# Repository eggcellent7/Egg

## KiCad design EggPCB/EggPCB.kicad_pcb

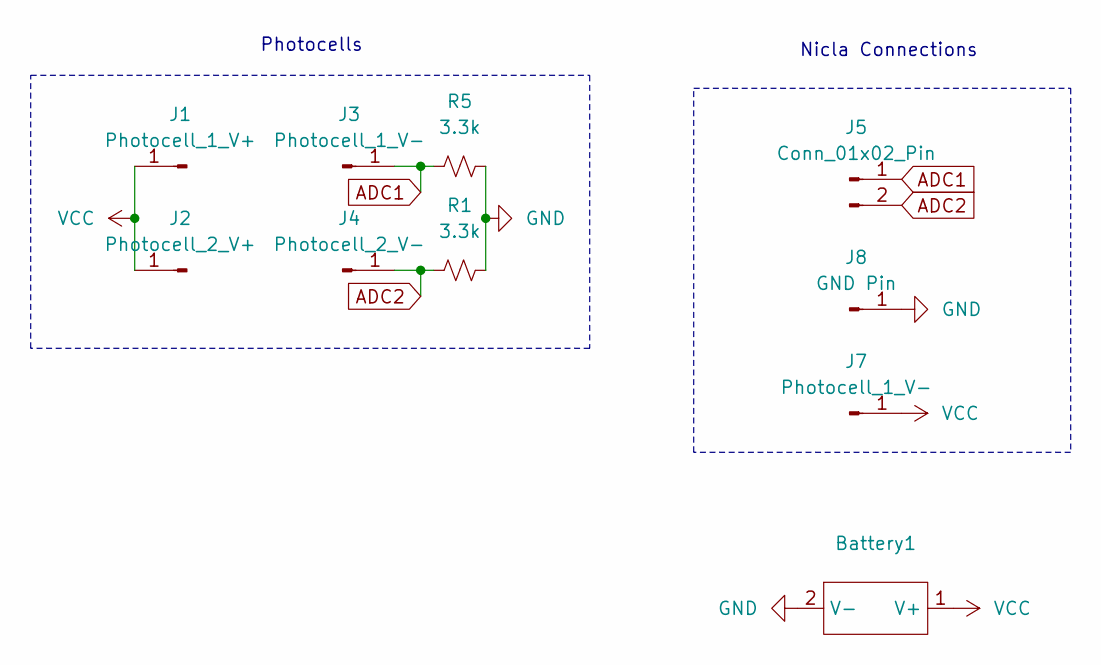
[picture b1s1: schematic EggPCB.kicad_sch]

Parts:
Battery1: CoinCellBat
J1: Photocell_1_V+; PinHeader_1x01_P2.54mm_Vertical
J2: Photocell_2_V+; PinHeader_1x01_P2.54mm_Vertical
J3, J7: Photocell_1_V-; PinHeader_1x01_P2.54mm_Vertical
J4: Photocell_2_V-; PinHeader_1x01_P2.54mm_Vertical
J5: Conn_01x02_Pin; PinHeader_1x02_P2.54mm_Vertical
J8: GND Pin; PinHeader_1x01_P2.54mm_Vertical
R1, R5: 3.3k; R_Axial_DIN0207_L6.3mm_D2.5mm_P7.62mm_Horizontal

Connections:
ADC1: J3.1, J5.1, R5.1
ADC2: J4.1, J5.2, R1.1
GND: Battery1.2 (V-), J8.1, R1.2, R5.2
VCC: Battery1.1 (V+), J1.1, J2.1, J7.1

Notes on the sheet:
Photocells
Nicla Connections

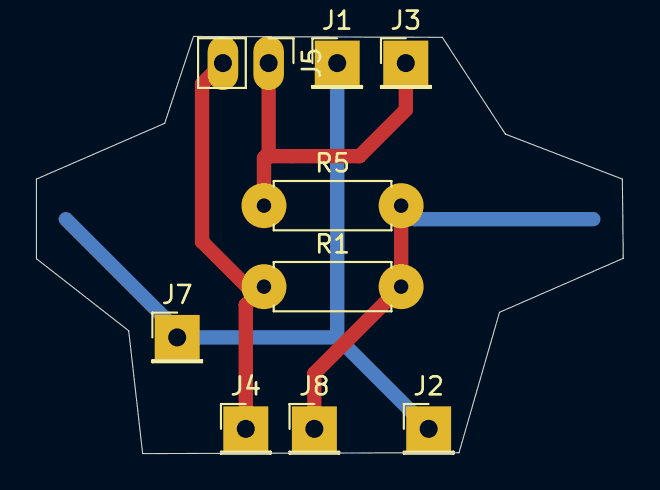
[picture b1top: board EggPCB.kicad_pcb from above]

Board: 2 copper layers, 32.6 x 23.2 mm, 10 parts (1 on the bottom side), 4 nets.

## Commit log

2025-06-10 added photoresistor test
2025-06-13 Added code for the nicla sense me
2025-06-13 Simple bluetooth
2025-06-16 Work done on bluetooth
2025-06-16 NimBLE connection was established
2025-06-16 Achieved almost all data to the substation with bluetooth
2025-06-16 Working on firebase
2025-06-17 Added RaspiSubstation
2025-06-17 BLE tests
2025-06-17 Wrapped ble in async
2025-06-17 Move adapter get into async
2025-06-17 Fixing syntax
2025-06-17 Another small syntax error
2025-06-17 Another small sytax error pt2
2025-06-18 Work done on python->nodejs connection
2025-06-18 Firebase setup and bluetooth setup connection
2025-06-18 push instead of append
2025-06-18 Python script should now be working
2025-06-18 firebase admin, uploading file to firebase
2025-06-18 forgot to add git ignore
2025-06-18 Forgot to add the ignore
2025-06-18 Working code kinda
2025-06-19 eggWrites reads complete data
2025-06-19 Updates to attempt to use notify system instead of constant polling
2025-06-23 Initialized firebase
2025-06-23 changed title
2025-06-24 defines functions to decode base64
2025-06-24 Converted base64 to floats
2025-06-24 changed header
2025-06-24 added package
2025-06-24 package lock
2025-06-24 made website more readable
2025-06-26 added graphs
2025-06-26 added egg model
2025-06-26 egg animation initial commit
2025-06-27 Lots of work done on nicla to raspi connection
2025-06-27 Added pcb
2025-06-30 Updates to pcb and work on the substation
2025-06-30 Added installer script for the raspi
2025-07-01 Temporarily erased model, only looks at 100 most recent points
2025-07-01 Nicla to Raspi connection should be working
2025-07-02 Rename new-folder-name/Egg-Schematics.txt to Egg-Schematic
2025-07-02 Schematic
2025-07-03 egg model
2025-07-03 deleted
2025-07-03 updated UI
2025-07-03 egg model rotates around center
2025-07-04 Work over past few days
2025-07-08 added download csv, user manual, and reorganized page
2025-07-08 Added animation rough draft
2025-07-08 recent changes
2025-07-08 Added extra characteristics to the bluetooth tests
2025-07-09 Added IDs tp niclas, having some bluetooth issues however
2025-07-09 Made bluetooth connection auto reconnect on the pi side
2025-07-09 Added error handling for timeouts
2025-07-09 Extended timeout and fixed error in error handling of timeout
2025-07-09 Fixed issue on raspi disconnects
2025-07-10 Updates to pcb to remove GPIO3 pin
2025-07-16 working version
2025-07-17 Working low power using resets
2025-07-17 Best Working version so far
2025-07-18 new data collection function
2025-07-18 Lowest Power consumption so far
2025-07-20 Small updates
2025-07-22 working presets
2025-07-23 Attempt to fix autostart on boot on the raspi
2025-07-25 added documentation link
2025-07-25 edited user manual
2025-07-27 Bluetooth will now retry until it works
2025-07-27 Added better handling to retry mechanism
2025-07-28 Fixed Sytax error with index.js
2025-07-28 Fixed sytax errors in index.js
2025-07-28 Better thread handling and made bluetooth retry sleep longer
2025-07-28 Added autorestart service to the bluetooth connection retry mechanism
2025-07-28 Fixed autorestart mechanism
2025-07-28 Fixed commented out lines
2025-07-28 Switched restart method
2025-07-31 Work on creating tab for substation controls
2025-07-31 Website now able to ping the substation and get live egg data
2025-08-02 Lot of work done to make the calibration sequence work
2025-08-05 A lot of issues have been fixed but still working on the catching
2025-08-05 Working Settings Updates except for id
2025-08-05 Nicla ID is able to be changes and fixed issue with disconnect errors
2025-08-06 Working file save and load back
2025-08-06 Added polling speed changes
2025-08-06 Last minute bug fixed
2025-09-14 Removed device name from tracked files
2025-11-06 Not working version
2025-11-10 Working on changes to make nicla work again
2025-11-11 Fixed issue relating to BHY2 begin causing disconnect to BLE
2025-11-11 Removed random tests from debugging
2025-11-11 Commented out debug flags by default
2025-12-07 Changes Zekiye made to the website
